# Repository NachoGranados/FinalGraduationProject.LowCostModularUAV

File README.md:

# FinalGraduationProject.LowCostModularUAV

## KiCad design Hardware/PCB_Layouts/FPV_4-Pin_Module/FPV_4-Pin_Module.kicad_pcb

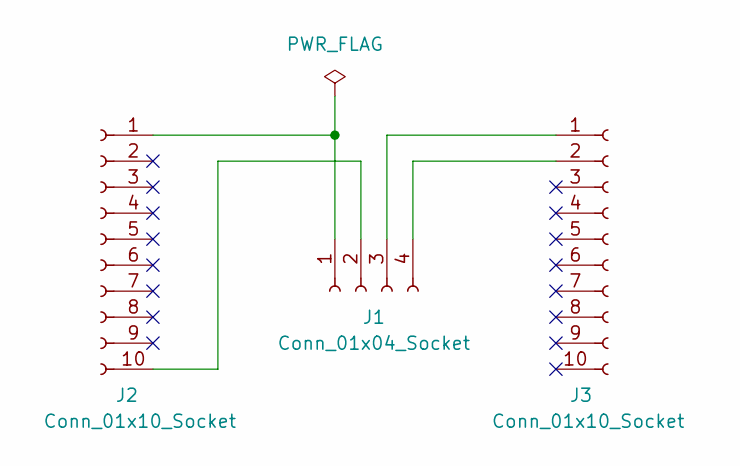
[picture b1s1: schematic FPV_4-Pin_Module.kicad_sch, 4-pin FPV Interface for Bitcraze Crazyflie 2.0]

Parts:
J1: Conn_01x04_Socket; JST_XH_B4B-XH-A_1x04_P2.50mm_Vertical
J2, J3: Conn_01x10_Socket; PinSocket_1x10_P2.00mm_Vertical

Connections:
unnamed: J1.1, J2.1
unnamed: J1.2, J2.10
unnamed: J1.3, J3.1
unnamed: J1.4, J3.2

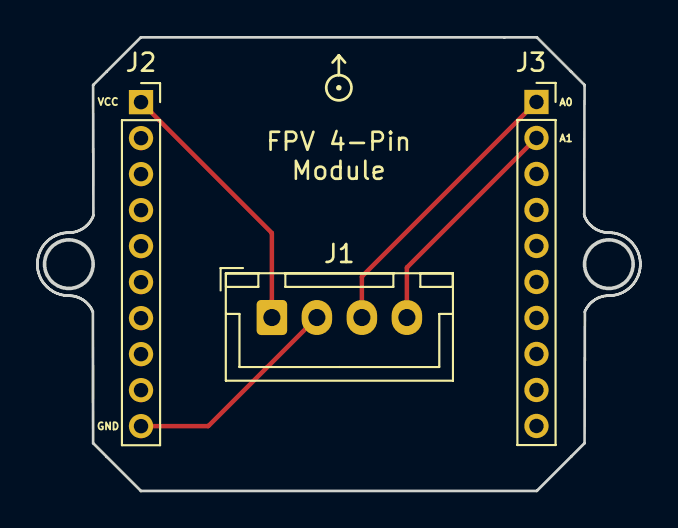
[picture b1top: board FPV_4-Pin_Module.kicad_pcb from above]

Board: 2 copper layers, 33.5 x 25.2 mm, 4 parts (0 on the bottom side), 4 nets.

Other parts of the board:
EXP_ORIENTATION: VAL**; EXP_ORIENTATION

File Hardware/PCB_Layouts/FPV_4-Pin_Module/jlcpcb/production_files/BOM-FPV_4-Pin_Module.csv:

Comment,Designator,Footprint,LCSC
Conn_01x04_Socket,J1,JST_XH_B4B-XH-A_1x04_P2.50mm_Vertical,
Conn_01x10_Socket,J2,PinSocket_1x10_P2.00mm_Vertical,
Conn_01x10_Socket,J3,PinSocket_1x10_P2.00mm_Vertical,

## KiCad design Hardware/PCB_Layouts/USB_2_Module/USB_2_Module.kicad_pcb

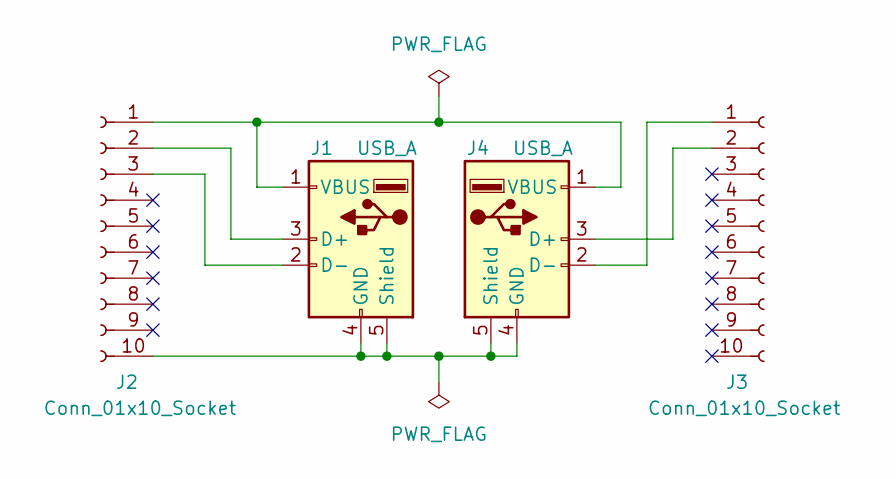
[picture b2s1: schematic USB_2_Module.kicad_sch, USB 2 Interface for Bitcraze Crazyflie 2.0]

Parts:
J1, J4: USB_A; USB_A_Stewart_SS-52100-001_Horizontal
J2, J3: Conn_01x10_Socket; PinSocket_1x10_P2.00mm_Vertical

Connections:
unnamed: J1.3 (D+), J2.2
unnamed: J1.2 (D-), J2.3
unnamed: J1.4 (GND), J1.5 (Shield), J2.10, J4.4 (GND), J4.5 (Shield)
unnamed: J1.1 (VBUS), J2.1, J4.1 (VBUS)
unnamed: J3.1, J4.2 (D-)
unnamed: J3.2, J4.3 (D+)

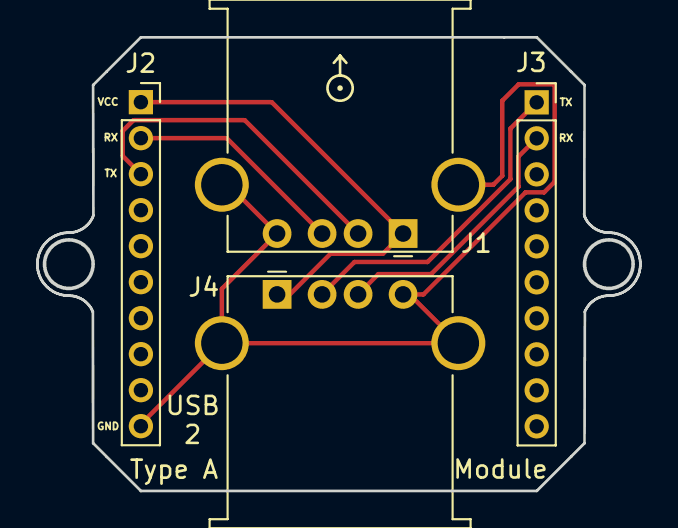
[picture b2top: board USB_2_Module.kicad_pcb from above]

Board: 2 copper layers, 33.5 x 25.2 mm, 5 parts (0 on the bottom side), 6 nets.

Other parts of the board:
EXP_ORIENTATION: VAL**; EXP_ORIENTATION

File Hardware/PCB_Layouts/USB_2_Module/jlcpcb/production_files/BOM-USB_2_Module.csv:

Comment,Designator,Footprint,LCSC
Conn_01x10_Socket,J3,PinSocket_1x10_P2.00mm_Vertical,
Conn_01x10_Socket,J2,PinSocket_1x10_P2.00mm_Vertical,
USB_A,J1,USB_A_Stewart_SS-52100-001_Horizontal,
USB_A,J4,USB_A_Stewart_SS-52100-001_Horizontal,

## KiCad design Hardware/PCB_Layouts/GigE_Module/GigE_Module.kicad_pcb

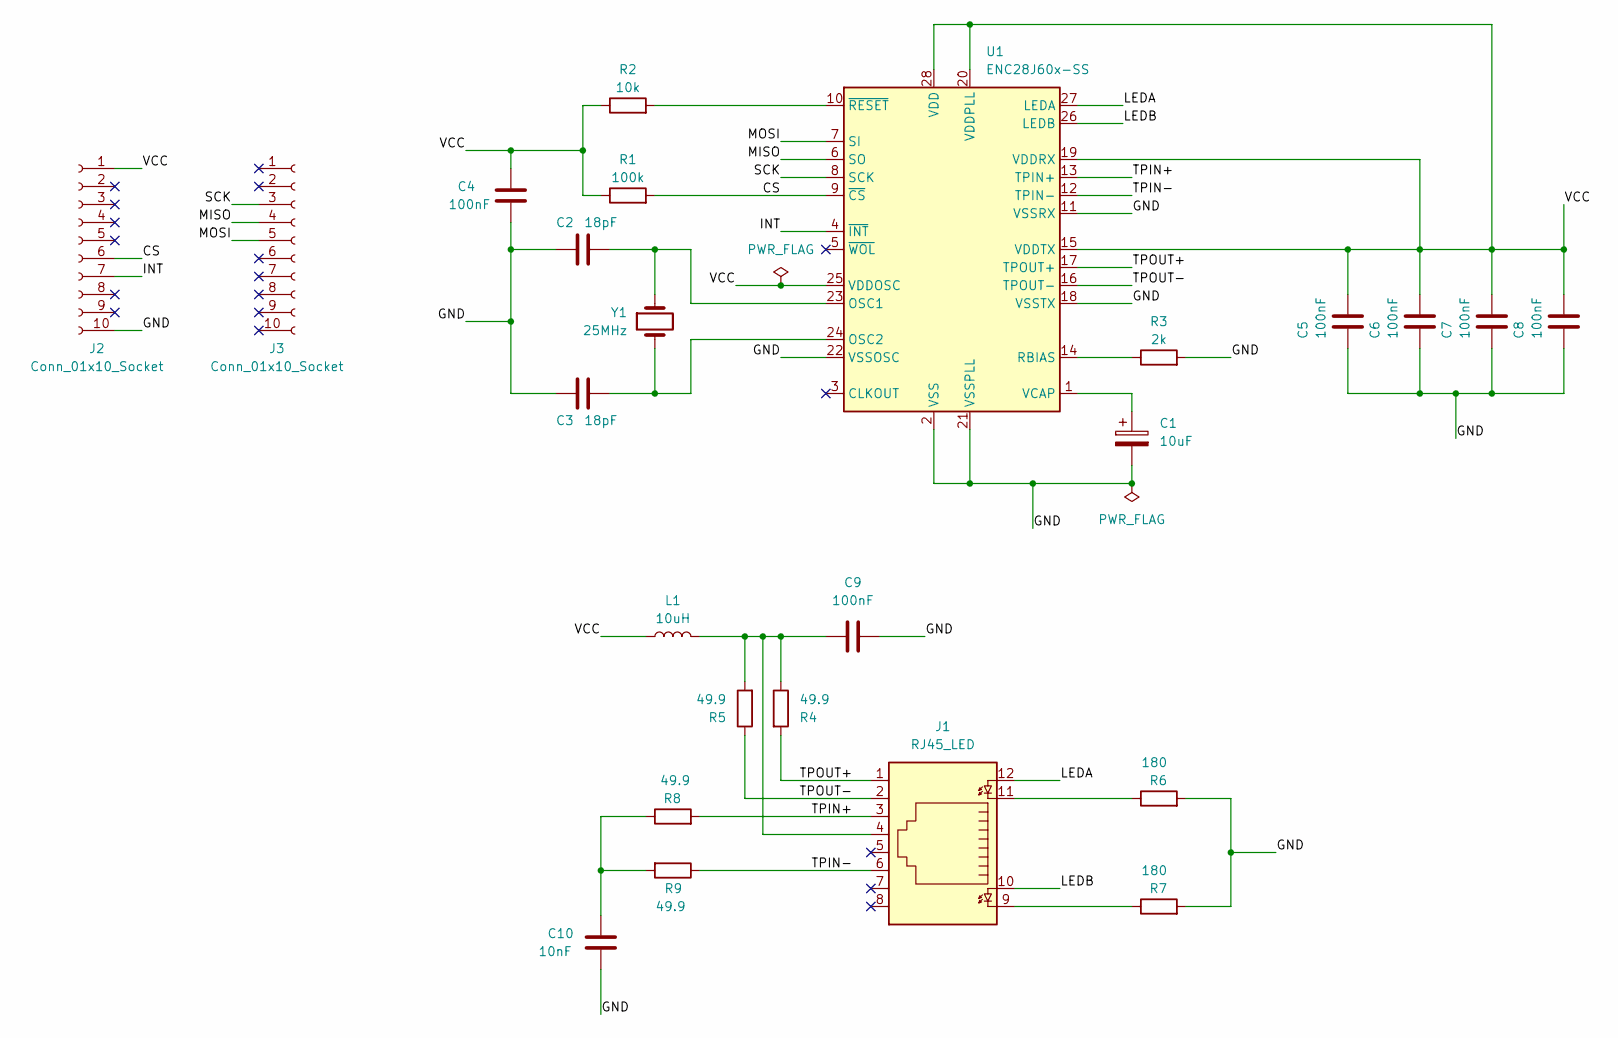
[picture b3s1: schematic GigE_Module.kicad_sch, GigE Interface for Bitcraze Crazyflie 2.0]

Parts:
C1: 10uF; CP_Elec_4x5.4
C2, C3: 18pF; C_0603_1608Metric
C4, C5, C6, C7, C8, C9: 100nF; C_0603_1608Metric
C10: 10nF; C_0603_1608Metric
J1: RJ45_LED; RJ45_Amphenol_RJHSE538X
J2, J3: Conn_01x10_Socket; PinSocket_1x10_P2.00mm_Vertical
L1: 10uH; L_0201_0603Metric_Pad0.64x0.40mm_HandSolder
R1: 100k; R_0603_1608Metric
R2: 10k; R_0603_1608Metric
R3: 2k; R_0603_1608Metric
R4, R5, R8, R9: 49.9; R_0603_1608Metric
R6, R7: 180; R_0603_1608Metric
U1: ENC28J60x-SS; SSOP-28_5.3x10.2mm_P0.65mm
Y1: 25MHz; Crystal_SMD_MicroCrystal_CC8V-T1A-2Pin_2.0x1.2mm

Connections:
/CS: J2.6, R1.2, U1.9 (~CS)
/GND: C1.2, C2.1, C3.1, C4.2, C5.2, C6.2, C7.2, C8.2, C9.2, C10.2, J2.10, R3.2, R6.2, R7.2, U1.2 (VSS), U1.11 (VSSRX), U1.18 (VSSTX), U1.21 (VSSPLL), U1.22 (VSSOSC)
/INT: J2.7, U1.4 (~INT)
/LEDA: J1.12, U1.27 (LEDA)
/LEDB: J1.10, U1.26 (LEDB)
/MISO: J3.4, U1.6 (SO)
/MOSI: J3.5, U1.7 (SI)
/SCK: J3.3, U1.8 (SCK)
/TPIN+: J1.3, R8.2, U1.13 (TPIN+)
/TPIN-: J1.6, R9.1, U1.12 (TPIN-)
/TPOUT+: J1.1, R4.2, U1.17 (TPOUT+)
/TPOUT-: J1.2, R5.1, U1.16 (TPOUT-)
/VCC: C4.1, C5.1, C6.1, C7.1, C8.1, J2.1, L1.1, R1.1, R2.1, U1.15 (VDDTX), U1.19 (VDDRX), U1.20 (VDDPLL), U1.25 (VDDOSC), U1.28 (VDD)
unnamed: C9.1, J1.4, L1.2, R4.1, R5.2
unnamed: C10.1, R8.1, R9.2
unnamed: J1.9, R7.1
unnamed: J1.11, R6.1
unnamed: C2.2, U1.23 (OSC1), Y1.1
unnamed: C3.2, U1.24 (OSC2), Y1.2
unnamed: R3.1, U1.14 (RBIAS)
unnamed: C1.1, U1.1 (VCAP)
unnamed: R2.2, U1.10 (~RESET)

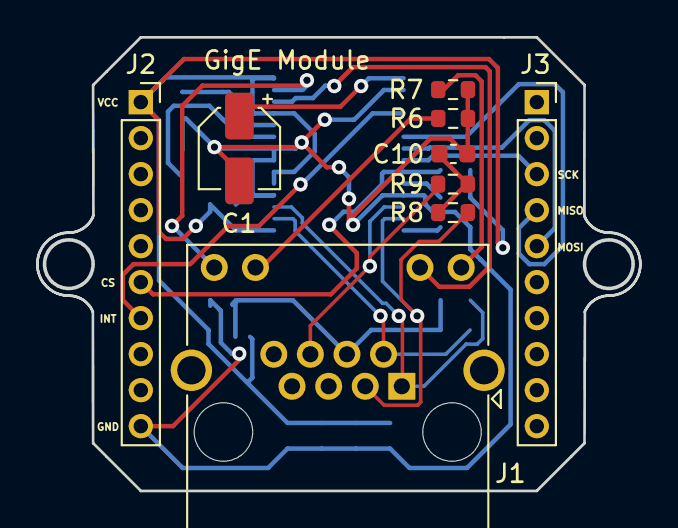
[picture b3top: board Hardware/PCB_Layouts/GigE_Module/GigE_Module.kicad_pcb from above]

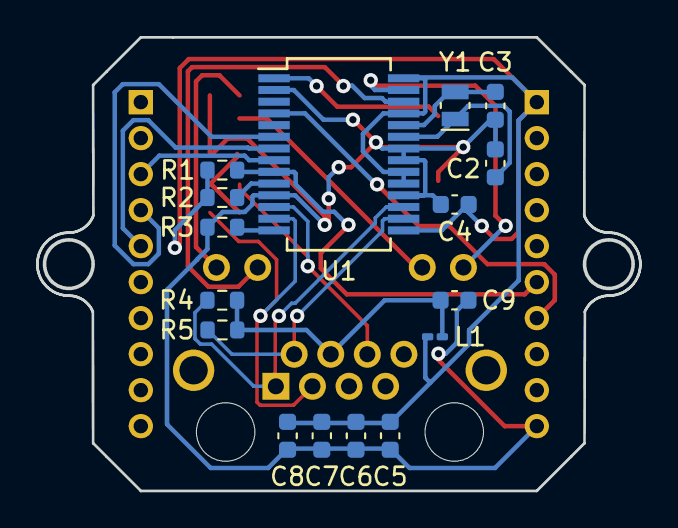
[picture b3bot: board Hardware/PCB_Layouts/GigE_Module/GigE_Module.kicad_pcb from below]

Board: 2 copper layers, 33.5 x 25.2 mm, 25 parts (16 on the bottom side), 22 nets.

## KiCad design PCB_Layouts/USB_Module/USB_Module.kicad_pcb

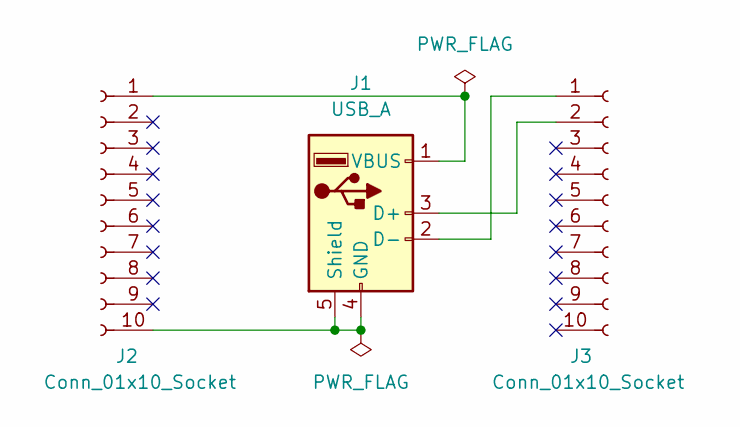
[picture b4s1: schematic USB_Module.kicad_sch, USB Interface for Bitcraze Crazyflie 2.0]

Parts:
J1: USB_A; USB_A_TE_292303-7_Horizontal
J2, J3: Conn_01x10_Socket; PinSocket_1x10_P2.00mm_Vertical

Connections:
unnamed: J1.3 (D+), J3.2
unnamed: J1.2 (D-), J3.1
unnamed: J1.4 (GND), J1.5 (Shield), J2.10
unnamed: J1.1 (VBUS), J2.1

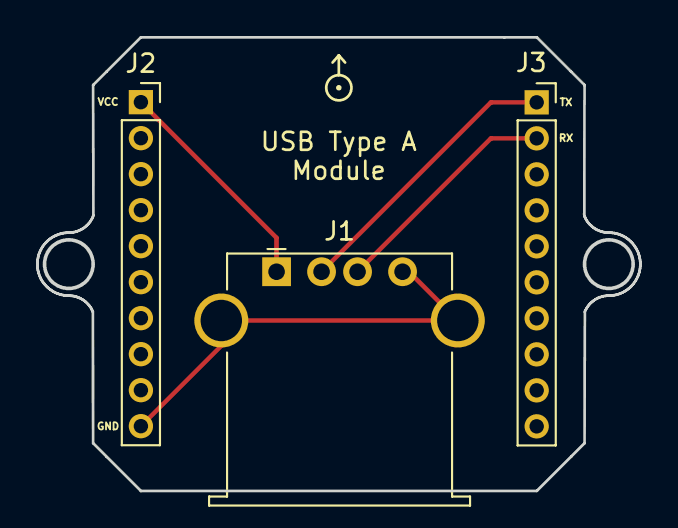
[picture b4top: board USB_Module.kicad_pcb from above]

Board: 2 copper layers, 33.5 x 25.2 mm, 4 parts (0 on the bottom side), 4 nets.

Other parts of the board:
EXP_ORIENTATION: VAL**; EXP_ORIENTATION

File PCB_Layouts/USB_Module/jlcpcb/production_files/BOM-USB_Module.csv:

Comment,Designator,Footprint,LCSC
USB_A,J1,USB_A_TE_292303-7_Horizontal,
Conn_01x10_Socket,J2,PinSocket_1x10_P2.00mm_Vertical,
Conn_01x10_Socket,J3,PinSocket_1x10_P2.00mm_Vertical,

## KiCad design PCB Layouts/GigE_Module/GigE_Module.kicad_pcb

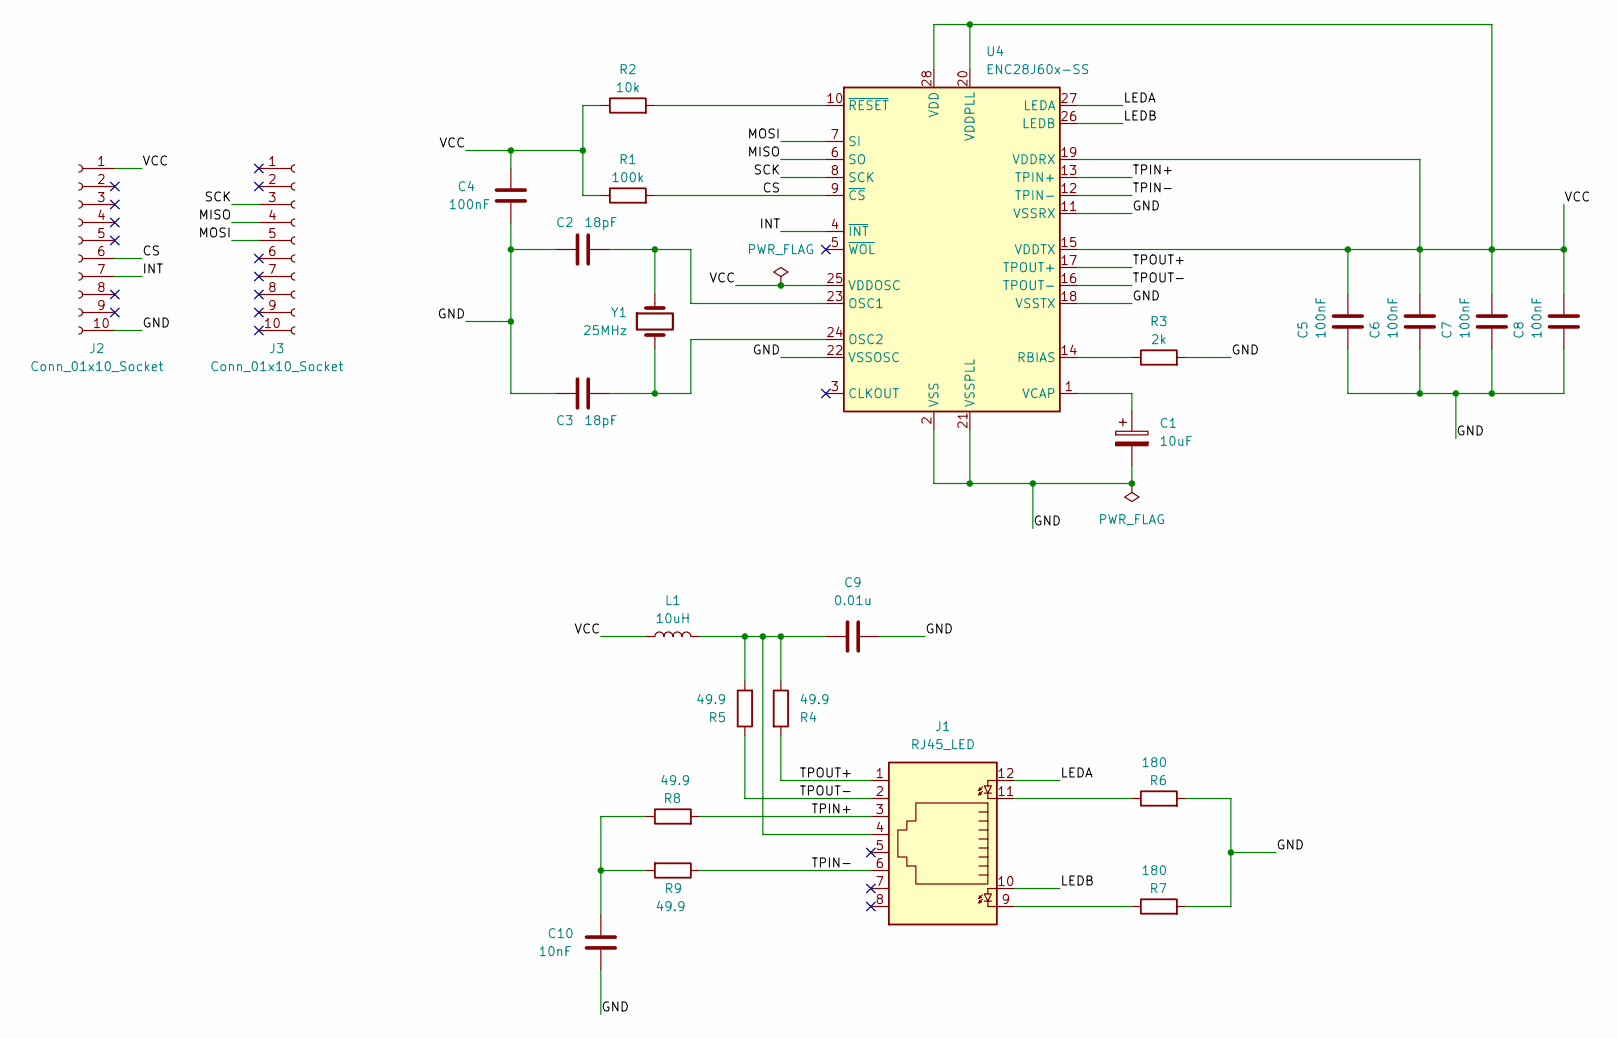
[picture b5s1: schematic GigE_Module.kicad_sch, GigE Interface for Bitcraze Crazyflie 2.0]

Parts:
C1: 10uF; CP_EIA-1608-08_AVX-J
C2, C3: 18pF; CP_EIA-1608-08_AVX-J
C4, C5, C6, C7, C8: 100nF; CP_EIA-1608-08_AVX-J
C9: 0.01u; CP_EIA-1608-08_AVX-J
C10: 10nF; CP_EIA-1608-08_AVX-J
J1: RJ45_LED; RJ45_Amphenol_RJHSE538X
J2, J3: Conn_01x10_Socket; PinSocket_1x10_P2.00mm_Vertical
L1: 10uH; L_0603_1608Metric
R1: 100k; R_0603_1608Metric
R2: 10k; R_0603_1608Metric
R3: 2k; R_0603_1608Metric
R4, R5, R8, R9: 49.9; R_0603_1608Metric
R6, R7: 180; R_0603_1608Metric
U4: ENC28J60x-SS; SSOP-28_5.3x10.2mm_P0.65mm
Y1: 25MHz; Crystal_SMD_MicroCrystal_CC4V-T1A-2Pin_5.0x1.9mm

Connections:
/CS: J2.6, R1.2, U4.9 (~CS)
/GND: C1.2, C2.1, C3.1, C4.2, C5.2, C6.2, C7.2, C8.2, C9.2, C10.2, J2.10, R3.2, R6.2, R7.2, U4.2 (VSS), U4.11 (VSSRX), U4.18 (VSSTX), U4.21 (VSSPLL), U4.22 (VSSOSC)
/INT: J2.7, U4.4 (~INT)
/LEDA: J1.12, U4.27 (LEDA)
/LEDB: J1.10, U4.26 (LEDB)
/MISO: J3.4, U4.6 (SO)
/MOSI: J3.5, U4.7 (SI)
/SCK: J3.3, U4.8 (SCK)
/TPIN+: J1.3, R8.2, U4.13 (TPIN+)
/TPIN-: J1.6, R9.1, U4.12 (TPIN-)
/TPOUT+: J1.1, R4.2, U4.17 (TPOUT+)
/TPOUT-: J1.2, R5.1, U4.16 (TPOUT-)
/VCC: C4.1, C5.1, C6.1, C7.1, C8.1, J2.1, L1.1, R1.1, R2.1, U4.15 (VDDTX), U4.19 (VDDRX), U4.20 (VDDPLL), U4.25 (VDDOSC), U4.28 (VDD)
unnamed: C9.1, J1.4, L1.2, R4.1, R5.2
unnamed: C10.1, R8.1, R9.2
unnamed: J1.9, R7.1
unnamed: J1.11, R6.1
unnamed: C2.2, U4.23 (OSC1), Y1.1
unnamed: C3.2, U4.24 (OSC2), Y1.2
unnamed: R3.1, U4.14 (RBIAS)
unnamed: C1.1, U4.1 (VCAP)
unnamed: R2.2, U4.10 (~RESET)

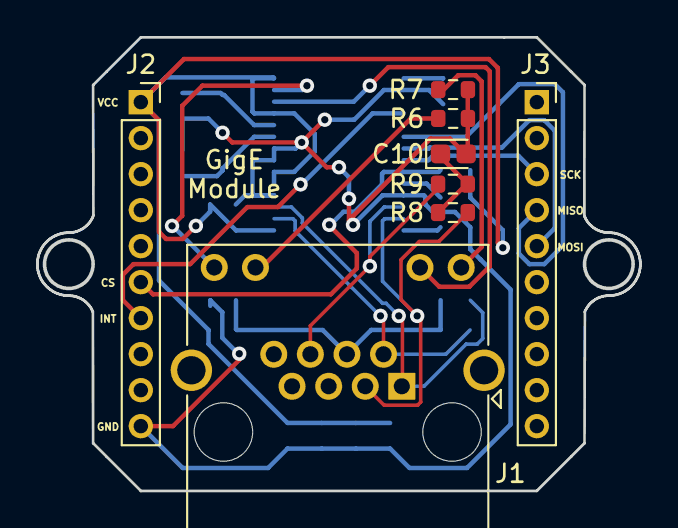
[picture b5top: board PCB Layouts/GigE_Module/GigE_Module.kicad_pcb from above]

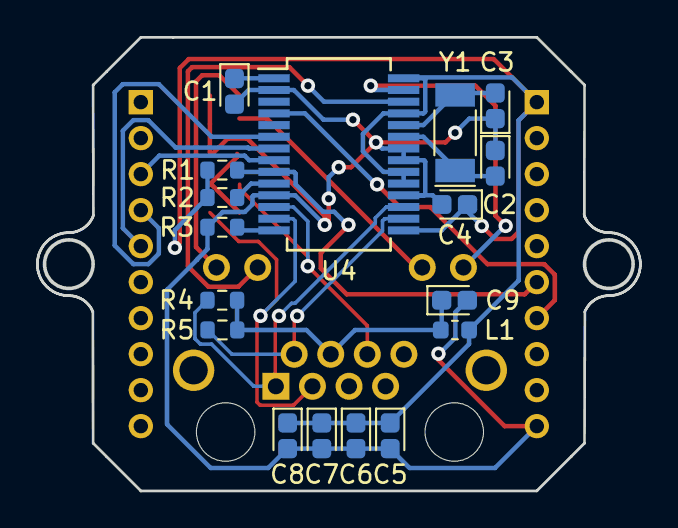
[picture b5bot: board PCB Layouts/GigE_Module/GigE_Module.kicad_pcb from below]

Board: 2 copper layers, 33.5 x 25.2 mm, 25 parts (17 on the bottom side), 22 nets.

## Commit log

2023-08-17 Adding the CSI-2 interface camera modules
2023-08-17 Adding the USB interface camera modules
2023-08-20 Adding the GPIO interface GPS module
2023-08-20 Adding the USB interface GPS module
2023-08-23 Adding the GPIO interface microphone module
2023-08-23 Adding the USB interface microphone modules
2023-08-23 Adding the GPIO interface IR sensor module
2023-08-29 Adding new camera module
2023-09-02 Adding USB camera results
2023-09-02 Adding USB microphone results
2023-09-04 Updating MIPI CSI-2 camera code files
2023-09-04 Updating USB camera code files
2023-09-04 Adding MIPI CSI-2 camera results
2023-09-04 Updating GPIO microphone code files
2023-09-04 Adding GPIO microphone results
2023-09-04 Updating USB microphone code files
2023-09-04 Updating GPIO Infrared code files
2023-09-04 Adding GPIO Infrared results
2023-09-04 Changing some file names
2023-09-20 Cloning outdoor-exploration-system repository
2023-09-20 Adding a copy of the drone template to each of the interfaces
2023-09-20 Fixing project copies
2023-09-21 Deleting unnecessary files
2023-09-21 Adding USB interface module
2023-09-21 Improving USB PCB design
2023-09-22 Updating USB PCB desing
2023-09-22 Adding GigE PCB design
2023-09-23 Adding first version of GigE PCB design
2023-09-24 Finishing GigE PCB design
2023-09-25 Modifying GPS USB python code and adding respective results
2023-09-26 Updating GigE PCB design
2023-09-26 Adding label pins in each PCB design
2023-10-03 Adding FPV 3-pin interface module
2023-10-03 Adding FPV 4-pin interface module
2023-10-04 Updating GPIO GPS python file
2023-10-04 Adding GPIO GPS results
2023-10-04 Adding the connections of each interface
2023-10-04 Updating Camera python files
2023-10-04 Updating GPS python files
2023-10-04 Updating microphone python files
2023-10-04 Adding interface user manual
2023-10-04 Unifying all interfaces
2023-10-04 Generating gerber files
2023-10-04 Generating gerber files of each interface module
2023-10-05 Updating gerber files of the unified design
2023-10-05 Updating necessary files for PCB quotes
2023-10-05 Updating the USB module to adapt to the quote
2023-10-06 Updating USB and GigE files for PCB quotes
2023-10-06 Adding GigE quote
2023-10-06 Adding USB quote
2023-10-06 Adding FPV 3 Pin quote
2023-10-06 Adding FPV 4 Pin quote
2023-10-06 PCB material upgrade from Standard to Economic on USB, FPV 3Pin and FPV 4 Pin modules
2023-10-06 Separating quotes into another folder
2023-10-06 Adding USB 2 module and quote
2023-10-07 Updating modular interfaces module and quote
2023-10-07 Adding Modular Interfaces No GigE module and quote
2023-10-09 Organizing each file in a new folder
2023-10-09 Adding Crazyflie 2.0 drone important files
2023-10-09 Adding Raspberry Pi 3B+ files
2023-10-10 Updating user manual
2023-10-15 Updating USB PCB design
2023-10-15 Updating FPV 3-pin PCB design
2023-10-15 Updating FPV 4-pin PCB design
2023-10-16 Adding project deliverables
